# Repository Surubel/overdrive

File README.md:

# overdrive
Brushless ESC based on Atmega8 (SimonK firmware)

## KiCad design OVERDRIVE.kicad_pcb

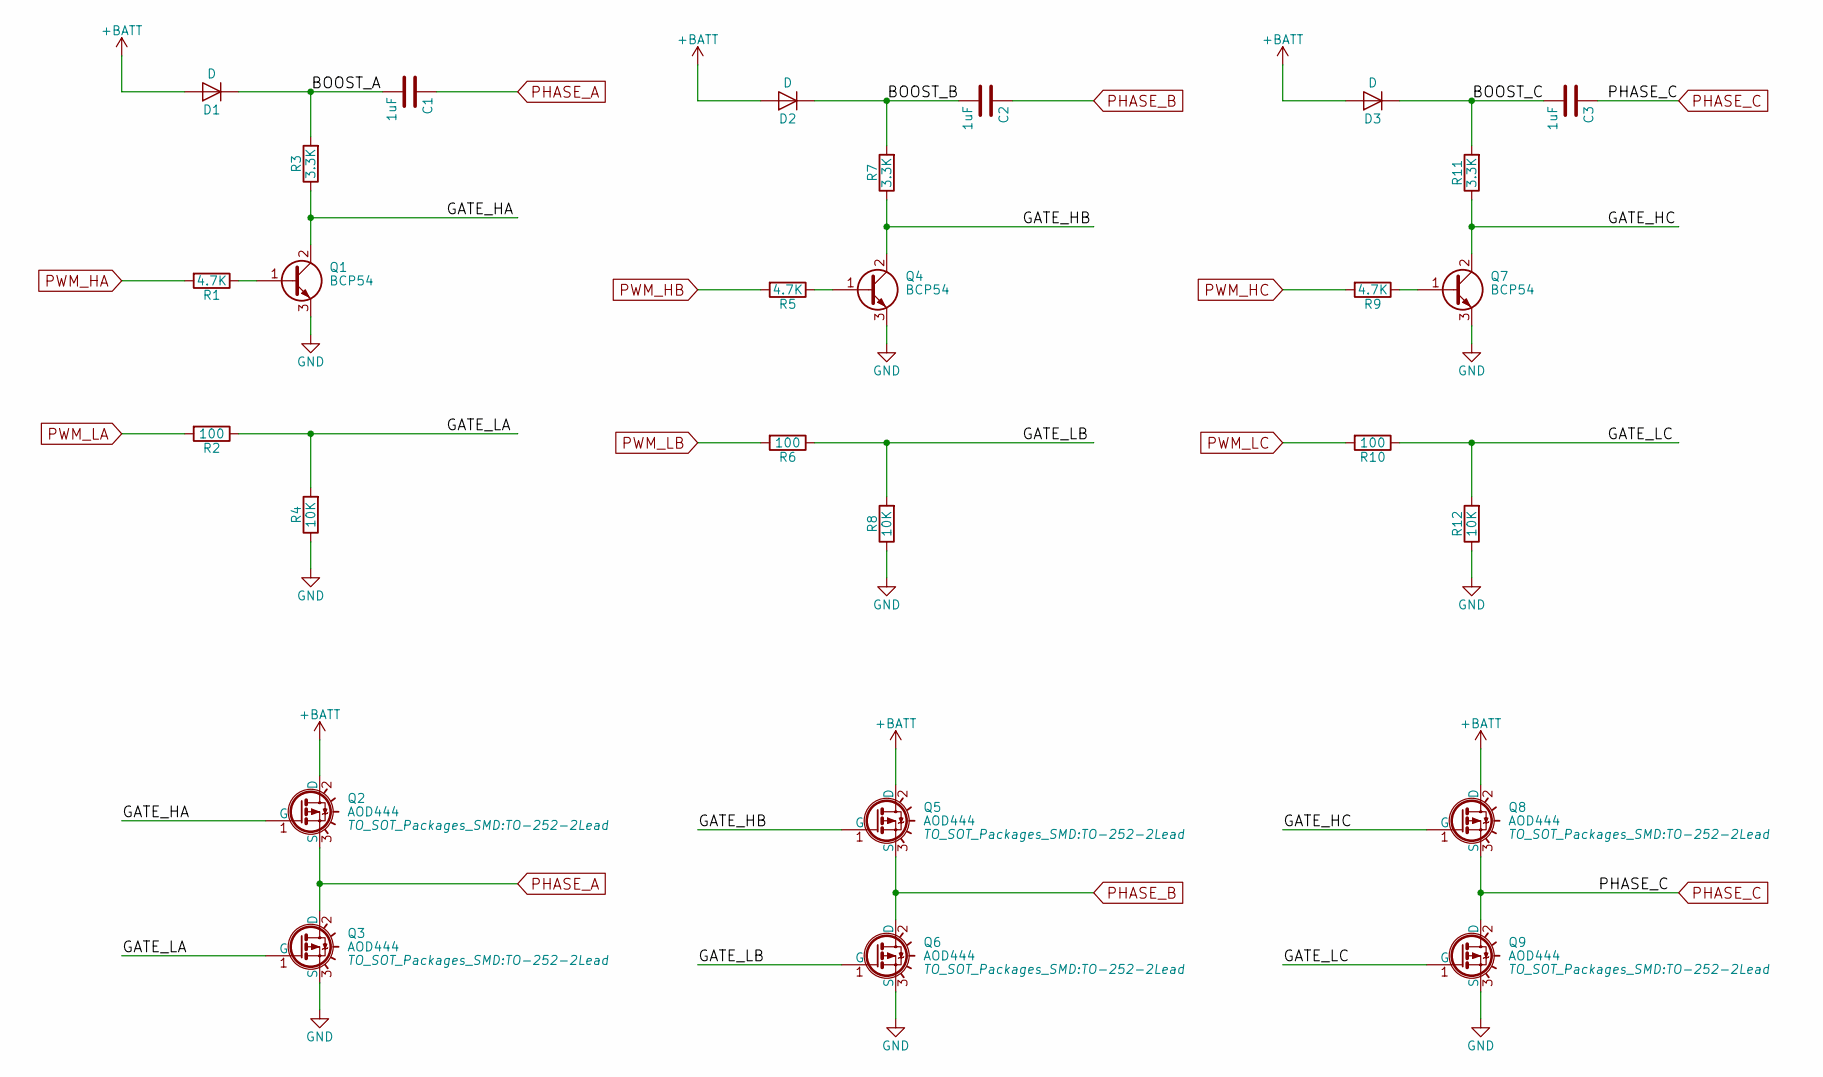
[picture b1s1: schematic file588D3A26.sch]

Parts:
C1, C2, C3: 1uF; C_0805_HandSoldering
D1, D2, D3: D; SMA_Standard
Q1, Q4, Q7: BCP54; SOT-223
Q2, Q3, Q5, Q6, Q8, Q9: AOD444; TO-252-2Lead
R1, R5, R9: 4.7K; R_0805_HandSoldering
R2, R6, R10: 100; R_0805_HandSoldering
R3, R7, R11: 3.3K; R_0805_HandSoldering
R4, R8, R12: 10K; R_0805_HandSoldering

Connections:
+BATT: D1.2 (A), D2.2 (A), D3.2 (A), Q2.2 (D), Q5.2 (D), Q8.2 (D); also elsewhere on the board
/3PHASE/BOOST_A: C1.2, D1.1 (K), R3.2
/3PHASE/BOOST_B: C2.2, D2.1 (K), R7.2
/3PHASE/BOOST_C: C3.2, D3.1 (K), R11.2
/3PHASE/GATE_HA: Q1.2 (C), Q2.1 (G), R3.1
/3PHASE/GATE_HB: Q4.2 (C), Q5.1 (G), R7.1
/3PHASE/GATE_HC: Q7.2 (C), Q8.1 (G), R11.1
/3PHASE/GATE_LA: Q3.1 (G), R2.1, R4.2
/3PHASE/GATE_LB: Q6.1 (G), R6.1, R8.2
/3PHASE/GATE_LC: Q9.1 (G), R10.1, R12.2
GND: Q1.3 (E), Q3.3 (S), Q4.3 (E), Q6.3 (S), Q7.3 (E), Q9.3 (S), R4.1, R8.1, R12.1; also elsewhere on the board
unnamed: Q1.1 (B), R1.1
unnamed: Q4.1 (B), R5.1
unnamed: Q7.1 (B), R9.1
PHASE_A: C1.1, Q2.3 (S), Q3.2 (D); also elsewhere on the board
PHASE_B: C2.1, Q5.3 (S), Q6.2 (D); also elsewhere on the board
PHASE_C: C3.1, Q8.3 (S), Q9.2 (D); also elsewhere on the board
PWM_HA: R1.2; also elsewhere on the board
PWM_HB: R5.2; also elsewhere on the board
PWM_HC: R9.2; also elsewhere on the board
PWM_LA: R2.2; also elsewhere on the board
PWM_LB: R6.2; also elsewhere on the board
PWM_LC: R10.2; also elsewhere on the board

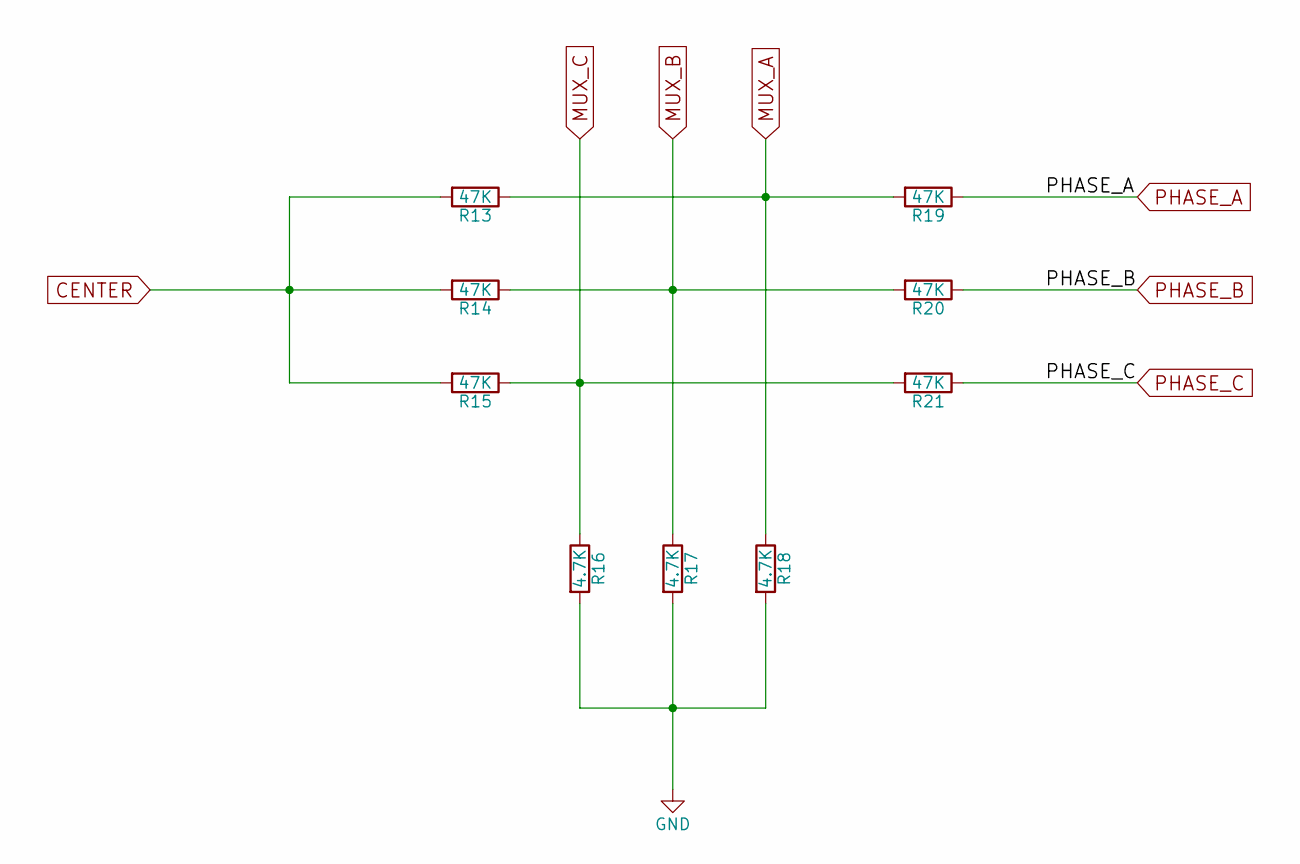
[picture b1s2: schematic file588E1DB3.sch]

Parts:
R13, R14, R15, R19, R20, R21: 47K; R_0805_HandSoldering
R16, R17, R18: 4.7K; R_0805_HandSoldering

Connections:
CENTER: R13.2, R14.2, R15.2; also elsewhere on the board
GND: R16.2, R17.2, R18.2; also elsewhere on the board
MUX_A: R13.1, R18.1, R19.2; also elsewhere on the board
MUX_B: R14.1, R17.1, R20.2; also elsewhere on the board
MUX_C: R15.1, R16.1, R21.2; also elsewhere on the board
PHASE_A: R19.1; also elsewhere on the board
PHASE_B: R20.1; also elsewhere on the board
PHASE_C: R21.1; also elsewhere on the board

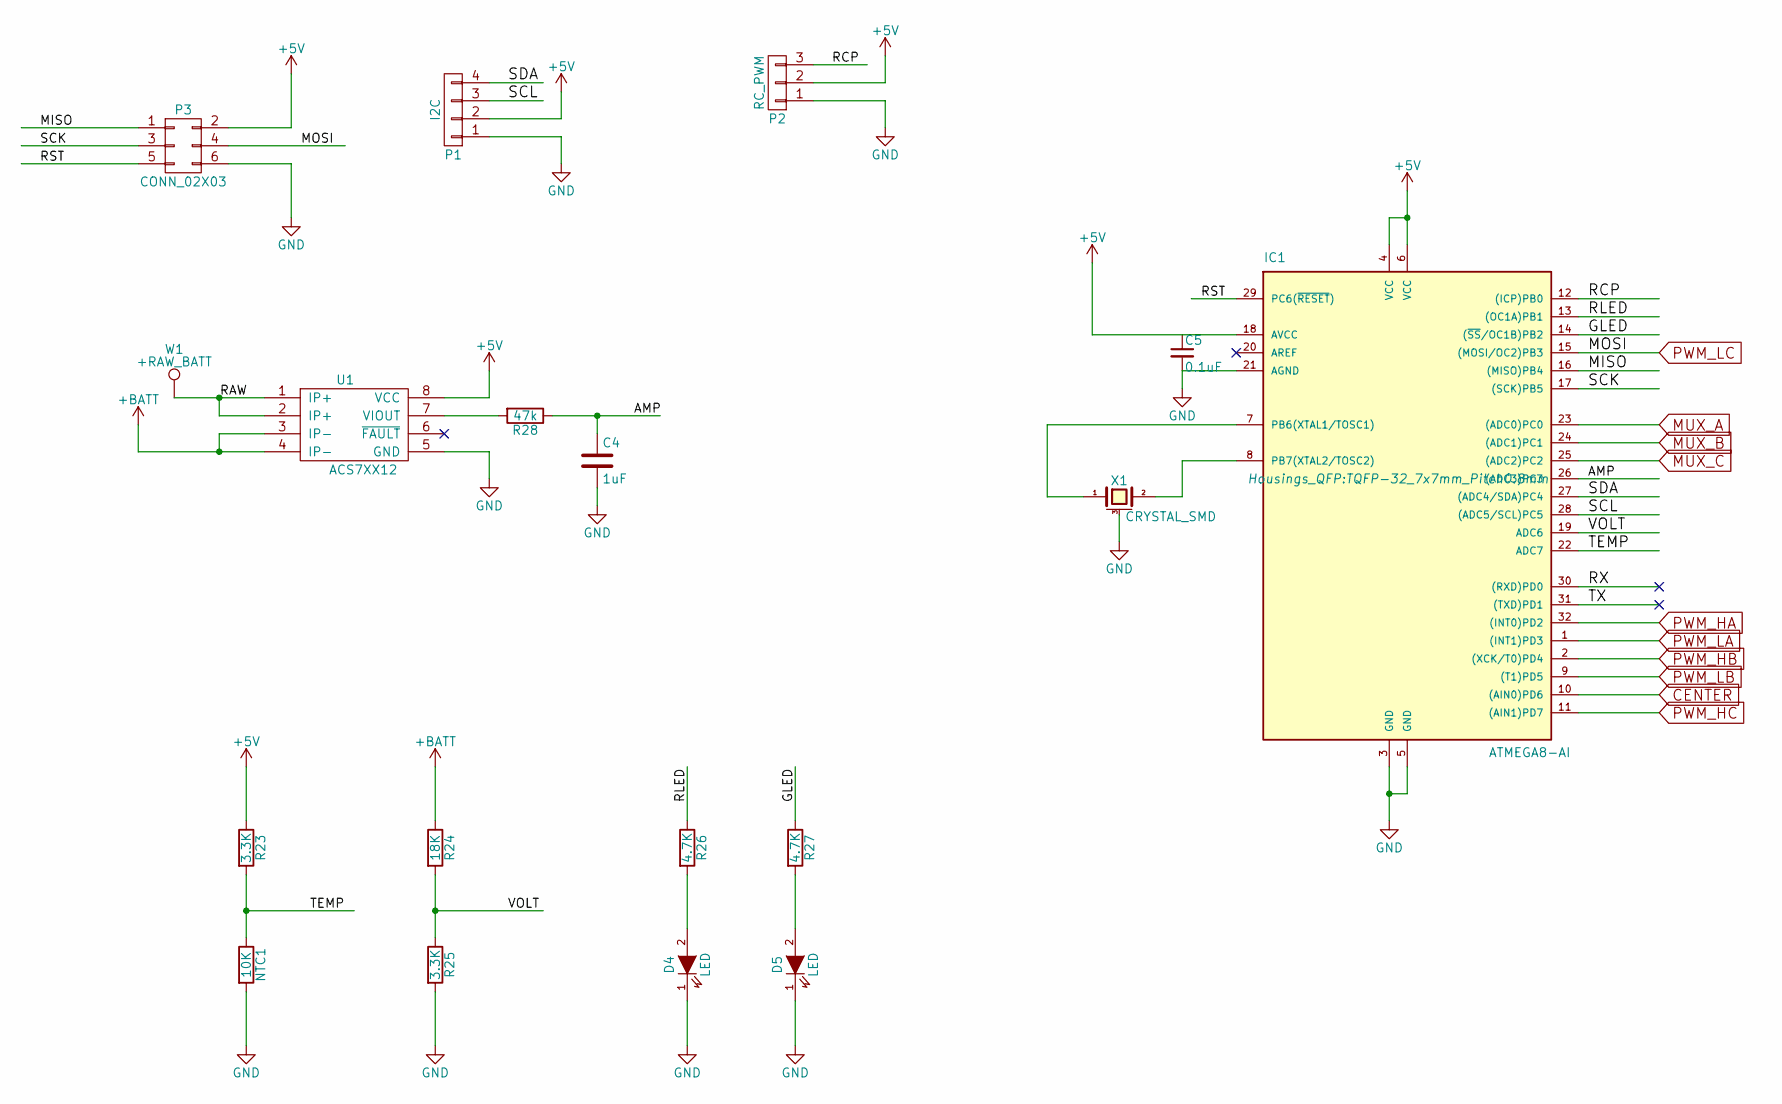
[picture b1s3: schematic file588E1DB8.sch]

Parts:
C4: 1uF; C_0805_HandSoldering
C5: 0.1uF; C_0805_HandSoldering
D4, D5: LED; LED_0805
IC1: ATMEGA8-AI; TQFP-32_7x7mm_Pitch0.8mm
NTC1: 10K; R_0805_HandSoldering
P1: I2C
P2: RC_PWM
P3: CONN_02X03; Pin_Header_Straight_2x03
R23, R25: 3.3K; R_0805_HandSoldering
R24: 18K; R_0805_HandSoldering
R26, R27: 4.7K; R_0805_HandSoldering
R28: 47k; R_0805_HandSoldering
U1: ACS7XX12; SOIC-8_3.9x4.9mm_Pitch1.27mm
W1: +RAW_BATT
X1: CRYSTAL_SMD; Resonator_7.2x3mm

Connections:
+5V: IC1.4 (VCC), IC1.6 (VCC), IC1.18 (AVCC), P1.2, P2.2, P3.2, R23.1, U1.8 (VCC); also elsewhere on the board
+BATT: R24.1, U1.3 (IP-), U1.4 (IP-); also elsewhere on the board
/uC/AMP: C4.1, IC1.26 ((ADC3)PC3), R28.1
/uC/GLED: IC1.14 ((~SS~/OC1B)PB2), R27.1
/uC/MISO: IC1.16 ((MISO)PB4), P3.1; also elsewhere on the board
/uC/RAW: U1.1 (IP+), U1.2 (IP+), W1.1
/uC/RCP: IC1.12 ((ICP)PB0), P2.3; also elsewhere on the board
/uC/RLED: IC1.13 ((OC1A)PB1), R26.1
/uC/RST: IC1.29 (PC6(~RESET~)), P3.5; also elsewhere on the board
/uC/RX: IC1.30 ((RXD)PD0)
/uC/SCK: IC1.17 ((SCK)PB5), P3.3; also elsewhere on the board
/uC/SCL: IC1.28 ((ADC5/SCL)PC5), P1.3; also elsewhere on the board
/uC/SDA: IC1.27 ((ADC4/SDA)PC4), P1.4; also elsewhere on the board
/uC/TEMP: IC1.22 (ADC7), NTC1.1, R23.2
/uC/TX: IC1.31 ((TXD)PD1)
/uC/VOLT: IC1.19 (ADC6), R24.2, R25.1
CENTER: IC1.10 ((AIN0)PD6); also elsewhere on the board
GND: C4.2, C5.2, D4.1 (K), D5.1 (K), IC1.3 (GND), IC1.5 (GND), IC1.21 (AGND), NTC1.2, P1.1, P2.1, P3.6, R25.2, U1.5 (GND), X1.3 (case); also elsewhere on the board
MUX_A: IC1.23 ((ADC0)PC0); also elsewhere on the board
MUX_B: IC1.24 ((ADC1)PC1); also elsewhere on the board
MUX_C: IC1.25 ((ADC2)PC2); also elsewhere on the board
unnamed: D4.2 (A), R26.2
unnamed: D5.2 (A), R27.2
unnamed: IC1.7 (PB6(XTAL1/TOSC1)), X1.1
unnamed: IC1.8 (PB7(XTAL2/TOSC2)), X1.2
unnamed: R28.2, U1.7 (VIOUT)
PWM_HA: IC1.32 ((INT0)PD2); also elsewhere on the board
PWM_HB: IC1.2 ((XCK/T0)PD4); also elsewhere on the board
PWM_HC: IC1.11 ((AIN1)PD7); also elsewhere on the board
PWM_LA: IC1.1 ((INT1)PD3); also elsewhere on the board
PWM_LB: IC1.9 ((T1)PD5); also elsewhere on the board
PWM_LC: IC1.15 ((MOSI/OC2)PB3), P3.4; also elsewhere on the board

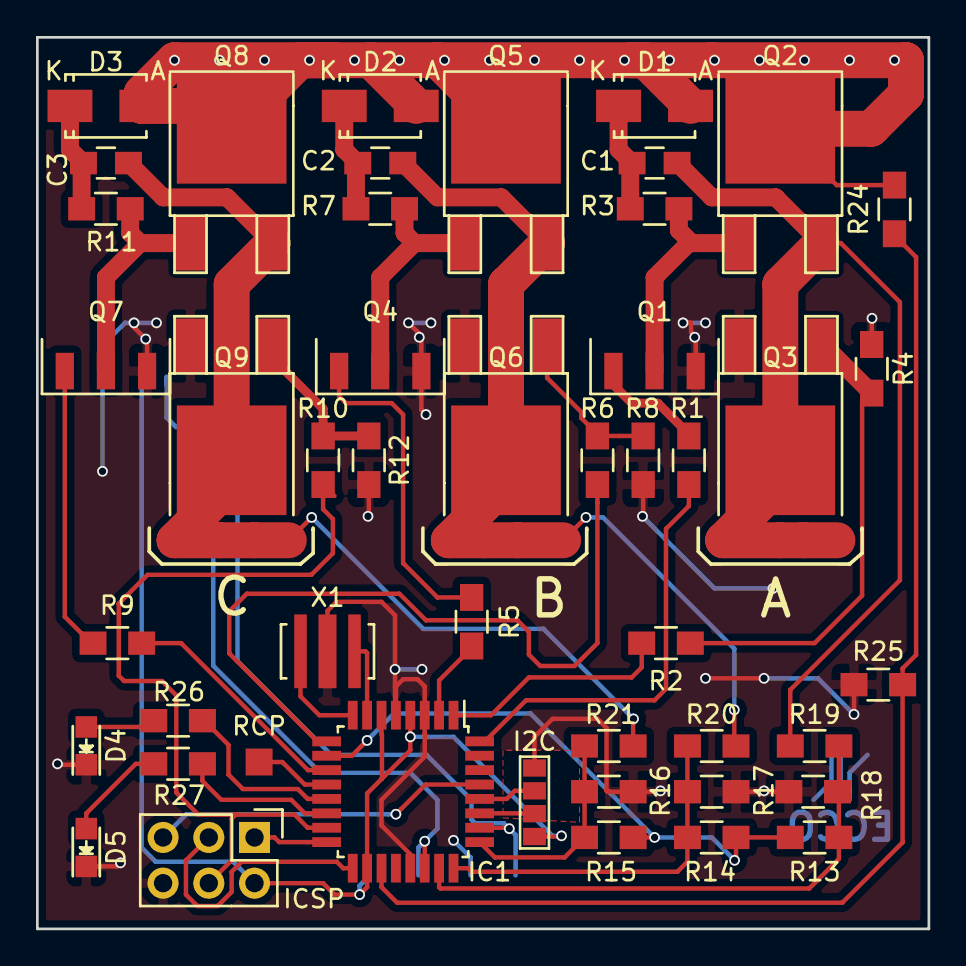
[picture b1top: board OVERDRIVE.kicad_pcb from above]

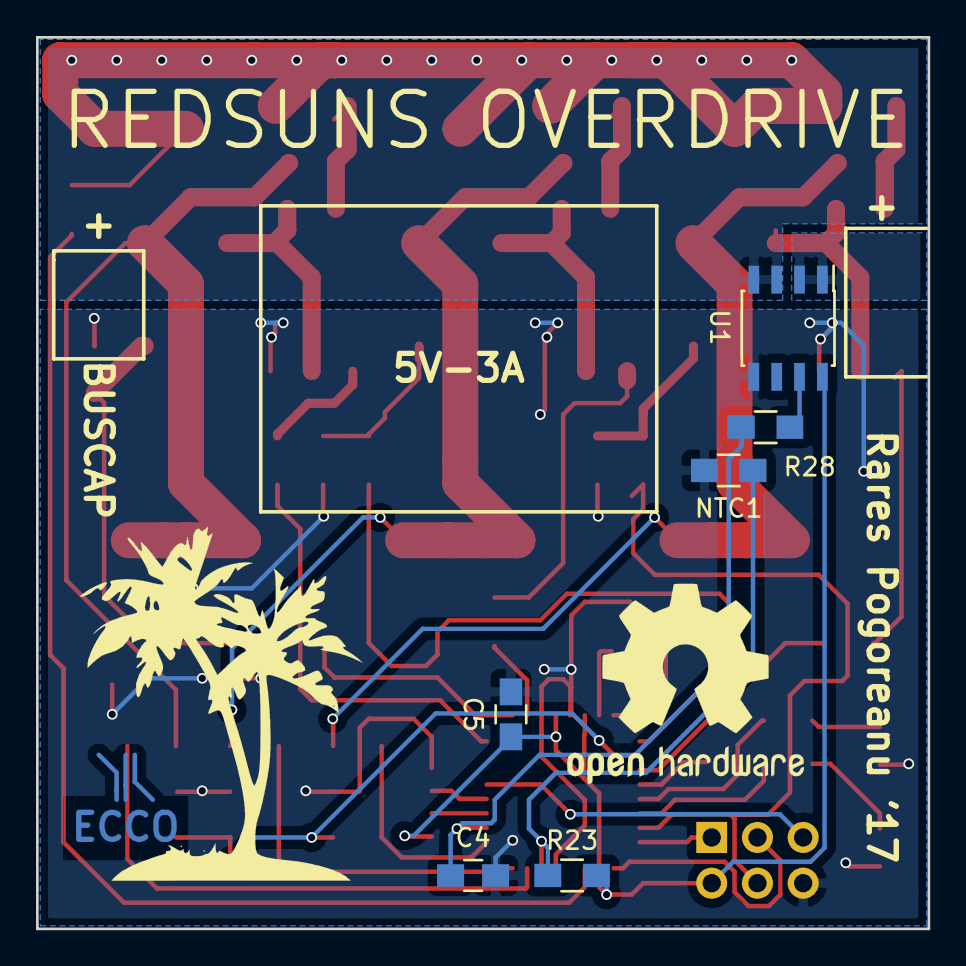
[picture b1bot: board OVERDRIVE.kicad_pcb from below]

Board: 2 copper layers, 49.5 x 49.5 mm, 53 parts (6 on the bottom side), 45 nets.

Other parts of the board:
I2C: GS3
ICSP: CONN_02X03; Pin_Header_Straight_2x03
RCP: Measurement_Point_Square-SMD-Pad_Small

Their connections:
+5V: I2C.4, ICSP.2; also elsewhere on the board
/uC/MISO: ICSP.1; also elsewhere on the board
/uC/RCP: RCP.1; also elsewhere on the board
/uC/RST: ICSP.5; also elsewhere on the board
/uC/SCK: ICSP.3; also elsewhere on the board
/uC/SCL: I2C.2; also elsewhere on the board
/uC/SDA: I2C.3; also elsewhere on the board
GND: I2C.1, ICSP.6; also elsewhere on the board
PWM_LC: ICSP.4; also elsewhere on the board
